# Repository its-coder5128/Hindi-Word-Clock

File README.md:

# Hindi-Word-Clock
A word clock is a type of clock that displays the time using words rather than numbers. 
Instead of using traditional clock hands or digital numbers, a word clock uses a grid of 
letters that light up to spell out the current time in words. 
The first word clocks were developed in the early 2000s, and they quickly gained 
popularity as a stylish and elegant alternative to traditional clocks. They are often 
appreciated for their simplicity, elegance, and the way they present time in a more 
intuitive and natural way.

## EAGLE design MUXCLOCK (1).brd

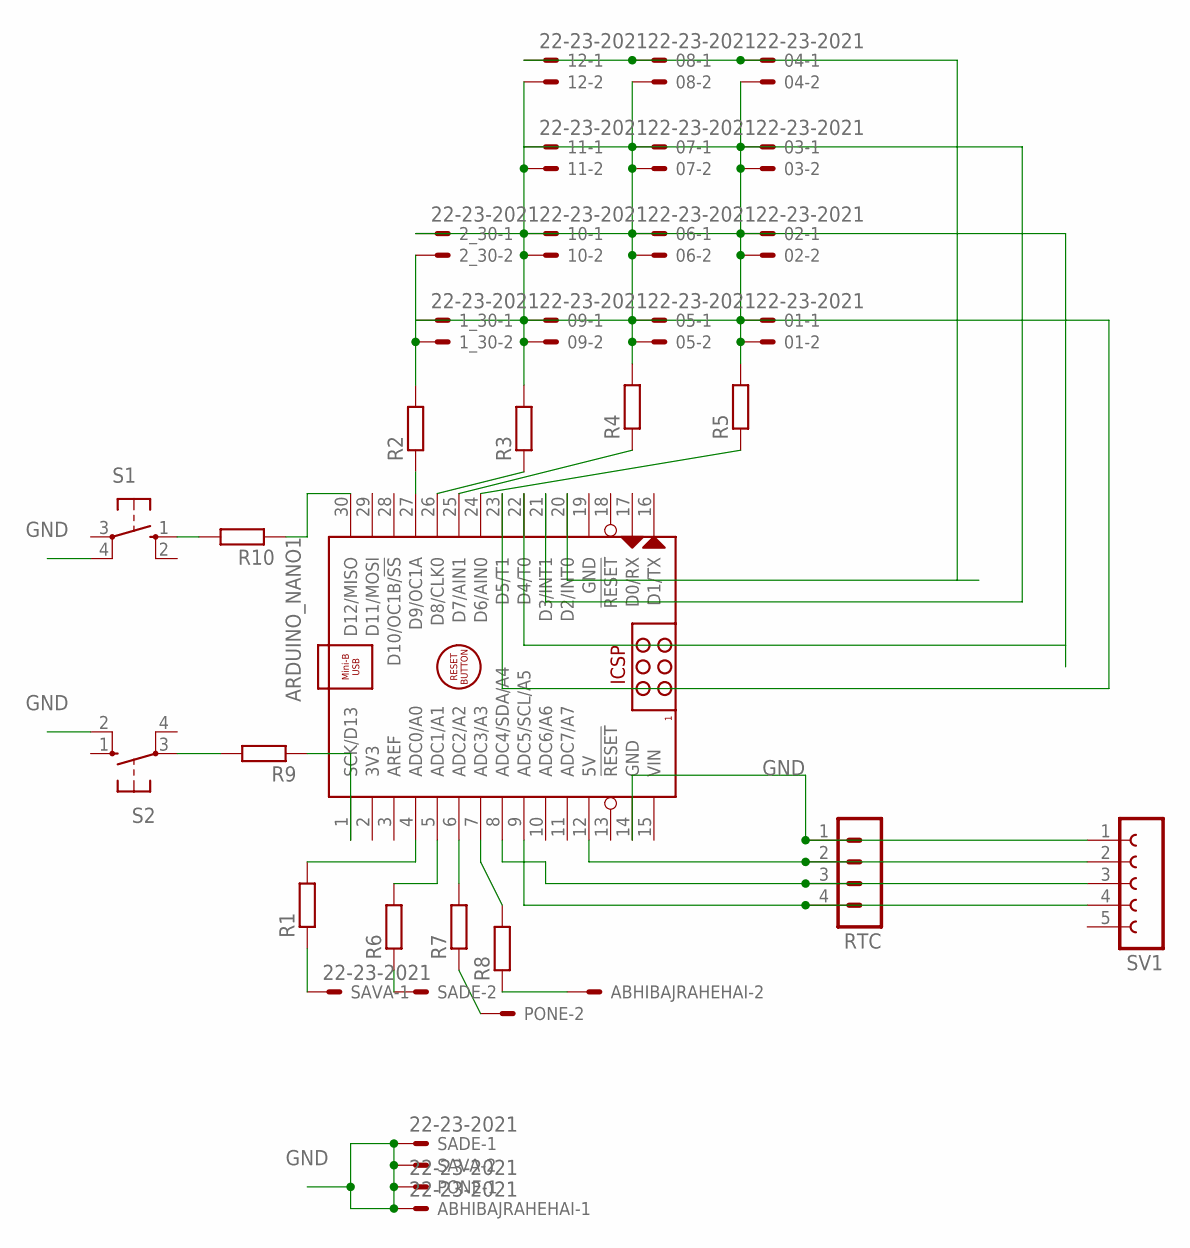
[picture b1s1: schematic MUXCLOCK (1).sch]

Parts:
01, 1_30, 02, 2_30, 03, 04, 05, 06, 07, 08, 09, 10, 11, 12: 22-23-2021
ABHIBAJRAHEHAI: 22-23-2021
ARDUINO_NANO1: ARDUINO_NANO
PONE: 22-23-2021
R1, R2, R3, R4, R5, R6, R7, R8, R9, R10: R-EU_0204/7; 0204/7
RTC: MA04-1
S1, S2: 10-XX; B3F-10XX
SADE: 22-23-2021
SAVA: 22-23-2021
SV1: FE05W

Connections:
GND: ABHIBAJRAHEHAI.1, ARDUINO_NANO1.14 (GND), ARDUINO_NANO1.19 (GND), PONE.1, RTC.1, S1.4 (P1), S2.2 (S1), SADE.1, SAVA.2, SV1.1
unnamed: ARDUINO_NANO1.27 (D9/OC1A), R2.1
unnamed: ARDUINO_NANO1.26 (D8/CLK0), R3.1
unnamed: ARDUINO_NANO1.25 (D7/AIN1), R4.1
unnamed: ARDUINO_NANO1.24 (D6/AIN0), R5.1
unnamed: 01.1, 1_30.1, 05.1, 09.1, ARDUINO_NANO1.23 (D5/T1)
unnamed: 02.1, 2_30.1, 06.1, 10.1, ARDUINO_NANO1.22 (D4/T0)
unnamed: 03.1, 07.1, 11.1, ARDUINO_NANO1.21 (D3/INT1)
unnamed: 04.1, 08.1, 12.1, ARDUINO_NANO1.20 (D2/INT0)
unnamed: 01.2, 02.2, 03.2, 04.2, R5.2
unnamed: 05.2, 06.2, 07.2, 08.2, R4.2
unnamed: 09.2, 10.2, 11.2, 12.2, R3.2
unnamed: 1_30.2, 2_30.2, R2.2
unnamed: ARDUINO_NANO1.4 (ADC0/A0), R1.2
unnamed: ARDUINO_NANO1.5 (ADC1/A1), R6.2
unnamed: ARDUINO_NANO1.6 (ADC2/A2), R7.2
unnamed: ARDUINO_NANO1.7 (ADC3/A3), R8.2
unnamed: R1.1, SAVA.1
unnamed: R6.1, SADE.2
unnamed: PONE.2, R7.1
unnamed: ABHIBAJRAHEHAI.2, R8.1
unnamed: ARDUINO_NANO1.1 (SCK/D13), R9.1
unnamed: R9.2, S2.3
unnamed: ARDUINO_NANO1.30 (D12/MISO), R10.1
unnamed: R10.2, S1.1 (S)
unnamed: ARDUINO_NANO1.12 (5V), RTC.2, SV1.2
unnamed: ARDUINO_NANO1.8 (ADC4/SDA/A4), RTC.3, SV1.3
unnamed: ARDUINO_NANO1.9 (ADC5/SCL/A5), RTC.4, SV1.4
VIN: ARDUINO_NANO1.15 (VIN)

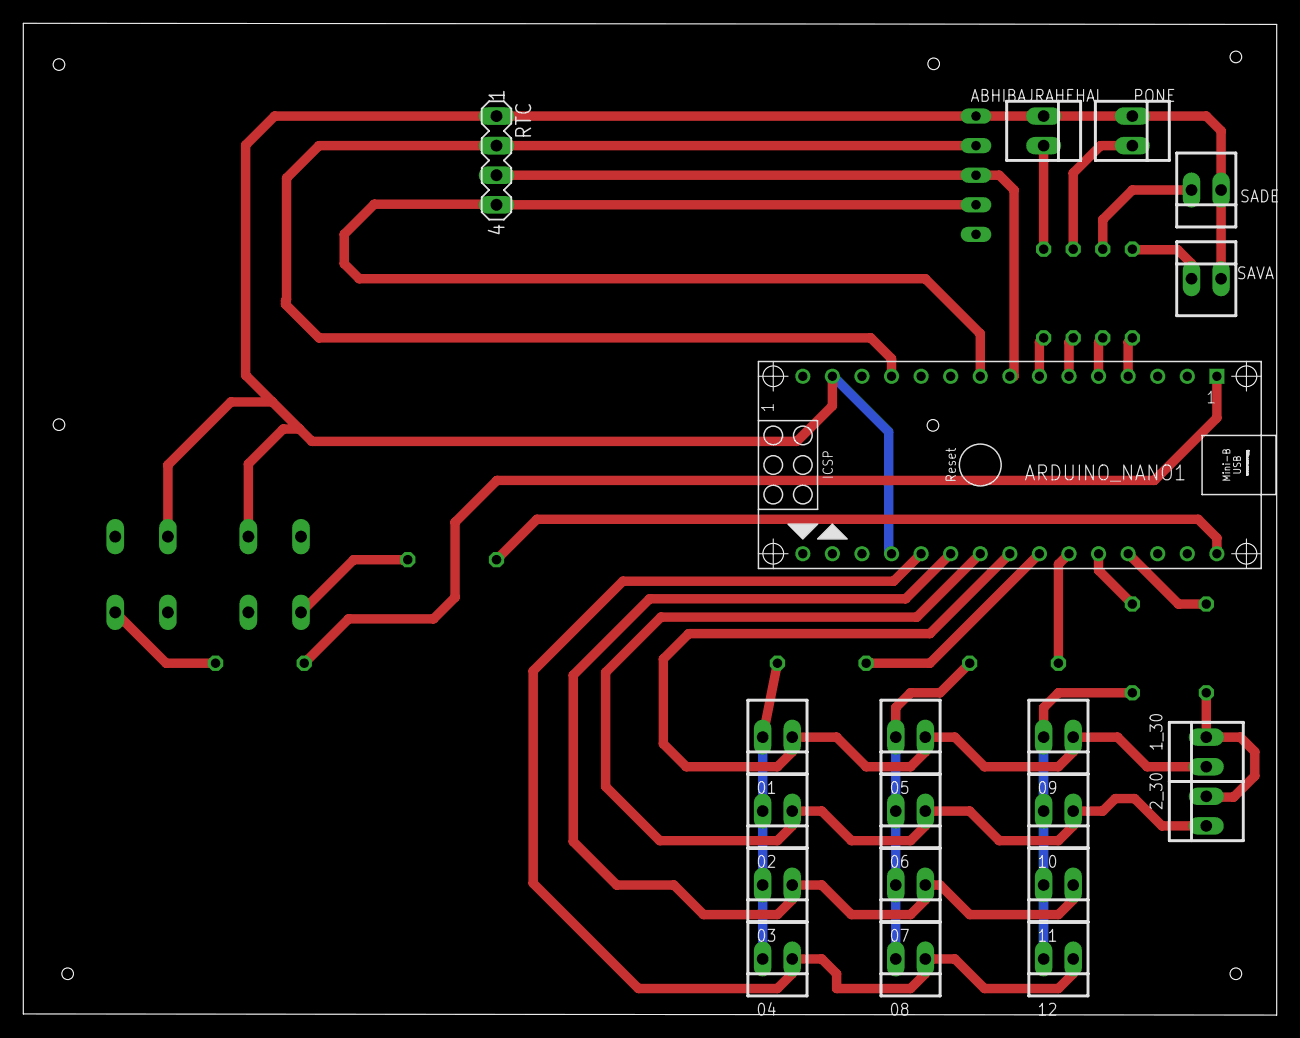
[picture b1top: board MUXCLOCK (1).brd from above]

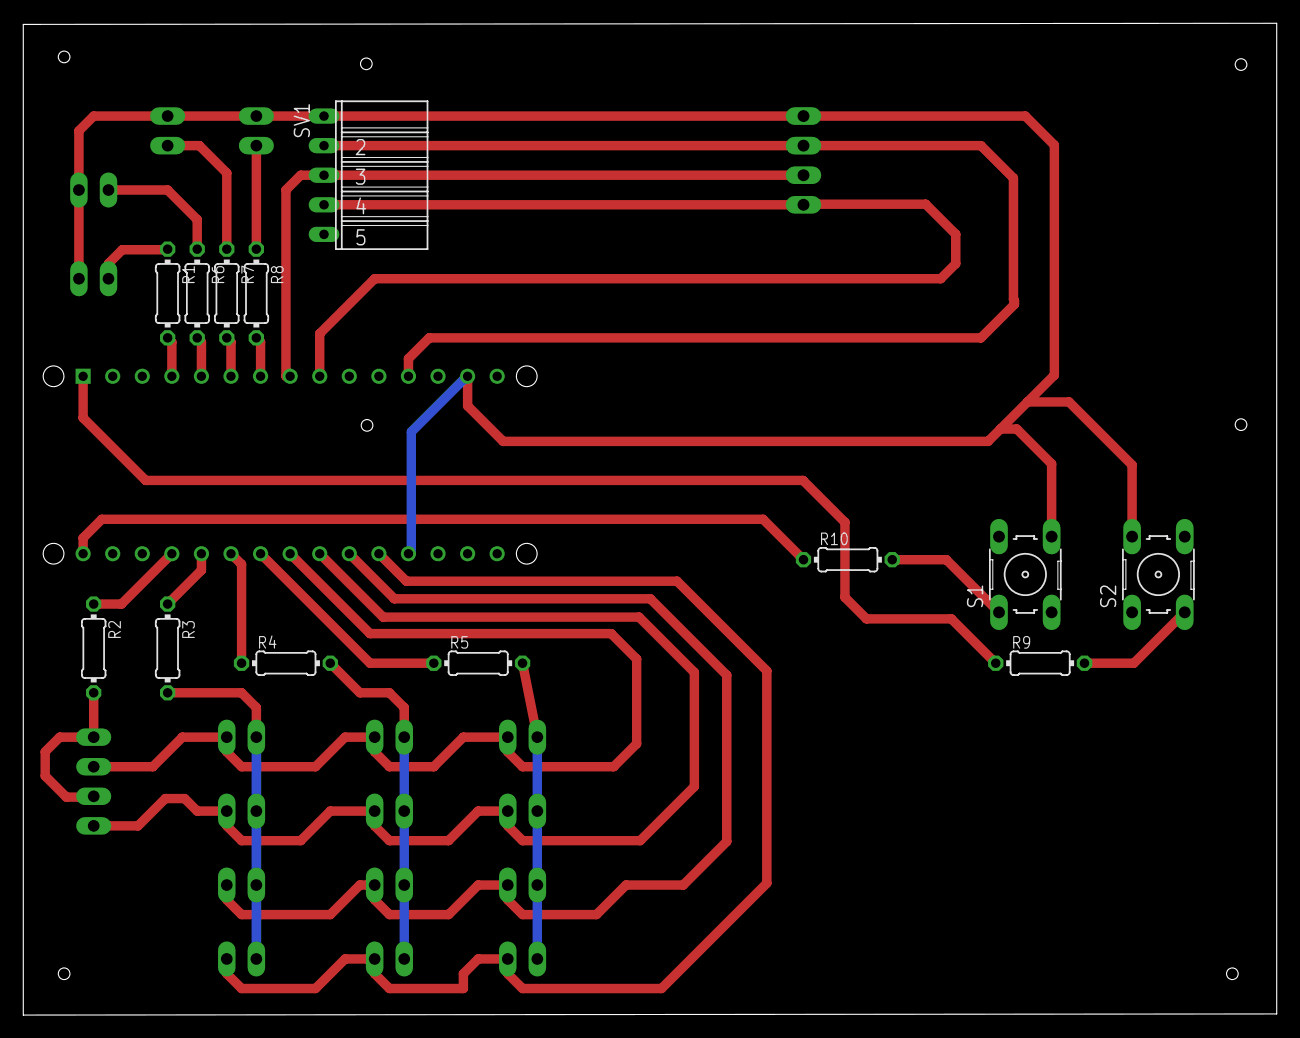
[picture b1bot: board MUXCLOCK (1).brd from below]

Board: 2 copper layers, 107.6 x 85.2 mm, 33 parts (13 on the bottom side), 28 nets.
